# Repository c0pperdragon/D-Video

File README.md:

# D-Video

A system to pump digital video out of vintage home computers.

While there are many mods available to make the video quality of old home computers and consoles
look better on modern displays, most of them are using analog technology (S-Video or RGB or such).
Analog signals are always prone to distortion and some rest of static noise always remains.

To overcome this problem and to get pixel-perfect quality identical to what an emulator could do, 
I have created a system that extracts the video information directly at the pins of the video chip
and transfer this signals to a converter that can generate crisp clear HDMI from it.
Clearly for every computer model there is a different way how to extract video information from the
video chip, and so the converter device must support all different signal types needed. 

That is done by using an FPGA that can be programmed to the meet the specific requirements 
of the system. For this I have designed my on FPGA board which I called the 
D-Video board that is based on a MAX 10 which is a pretty cheap device in comparison
with more powerful chips. With 8K elements and about 380kBit of memory, it just
covers what I need for my projects.

To feed the data into this FPGA, an additional modification board for each computer is needed
that converts the voltages from the pins to 3.3V levels. 

Currently supported devices:
	Atari 800 XL PAL   (probably every 8-bit Atari PAL)

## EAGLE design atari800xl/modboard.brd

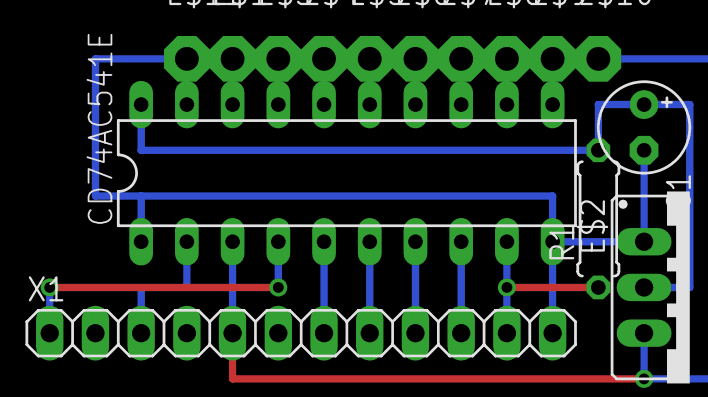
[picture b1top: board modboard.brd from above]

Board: 2 copper layers, 15 parts (0 on the bottom side), 11 nets.

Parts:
C1: 100n; E2,5-5
CD74AC541E: DIL20
E$1, E$3, E$4, E$5, E$6, E$7, E$8, E$9, E$10, E$11: PAD-01
E$2: 78XXS
R1: 1000; 0207/7
X1: 1X12

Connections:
S$1: CD74AC541E.3, E$2.OUT, X1.5
S$2: C1.-, CD74AC541E.1, CD74AC541E.10, CD74AC541E.19
S$3: CD74AC541E.9, R1.1
S$8: CD74AC541E.17, E$3.1
S$9: C1.+, CD74AC541E.20, E$2.GND, R1.2
S$11: CD74AC541E.16, E$4.1
S$12: CD74AC541E.15, E$5.1
S$13: CD74AC541E.14, E$6.1
S$14: CD74AC541E.13, E$7.1
S$15: CD74AC541E.12, E$8.1
S$16: CD74AC541E.11, E$9.1

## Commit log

2016-08-21 :tada: Added .gitattributes & .gitignore files
2016-08-21 Initial check-in
2016-08-25 Redesigned mod board for the Atari 800 XL
2016-09-04 binary file created by quartus (?)
2016-09-11 Teak color detection.
2016-11-18 Split hardware
    Hardware is now divided into Cylcone V GX Starter Kit (the upscaler) and
    a MAX V CPLD (on a DeltaBoard) as the D-Video signal generator.
2016-12-28 Continue implementing GTIA emulation
2016-12-29 Now using the HALT signal to trigger DMA
2017-02-05 Work in progress
2017-02-10 Designed PCB for the C64 mod board
2017-02-19 Last attempt to decode analog signals
    After trying pretty everything, the video signal can not be decoded
    reliably. On color changes the col signal is so distorted that it is not
    possible to find out what the new color of this pixel should be.
2017-02-25 custom fpga board
2017-02-28 Ongoing development fpga board
2017-03-02 finished pcb design
2017-03-21 first working program on the dvideo-board (lead blinker)
2017-03-25 Sucessful run of a test pattern generator
2017-03-29 Integrate GTIA emulation into D-Video board.
2017-03-31 Implemented VDELAY handling
    This was the last of the documented featues of the GTIA. I finally
    included it, even if nobody ever seemed to use it anyway...
2017-04-08 Revision 2 of the D-Video board
    Smaller overall size, GPIO on opposite edge of HDMI plug, mounting
    holes, no input voltage translators
2017-04-09 Restructured code - seperate projects for applications
2017-04-10 Rev. 2 Gerber files
2017-04-29 bill of materials
2017-05-05 Restructured sources
    Make extra folder for shared VHDL code and seperate folder for each
    target computer (atari,c64,spectrum,etc.).
2017-05-25 Ongoing development
    Try to read monitor info.
    Want to bring board Rev.2 to work (no luck yet)
2017-05-27 Made Atari 800 mod run on the Rev.2 board
2017-06-18 Improving signal compatibility
    It seems that many monitors refuse to work with my trick to add/remove a
    few clocks in each frame to synchronize the output to the input.
    Therefore I try to tightly couple the output frequency to the input
    frequency via a PLL. To make this again work, it is necessary to adjust
    the output video timings a bit. I hope this is will be more compliant
    then...
2017-06-23 Tinkering with the Timings for PAL and NTSC
2017-06-25 Use Atari clock to drive the HDMI
    Because the PLL on the D-Video board can not properly lock to the 3.5Mhz
    from the atari pixel clock, I am now using the PAL carrier frequency
    clock (about 4.4Mhz) instead. While this is still a bit out of spec for
    the PLL (5Mhz minimum) this seems to work now.
2017-06-29 Functional version for 3 different screen sizes
    After much fiddling around, I got the mod working for all my displays:
    1280x1024, 1640x1080, 1920x1080, all 50Hz.
    This stretches the standard quite a bit and uses the PLL out of spec,
    but thats the best I can do...
2017-06-30 Clean up and move changes to atarimod rev.2
2017-07-07 General cleanup, Schematics for the Atari modification
2017-07-15 Tweak frame start detection
2018-08-10 more tests...
2018-11-04 Remove trash, resolution tests
2019-05-04 Upscaler from YPbPr to HDML
    Just to have a working test environment to check the output of the YPbPr mod board agains the composite video of the C64.
2019-05-04 Tweak color transformation
2019-06-15 Calibrate for PAL upscaling
    To test the C64 enhancement board, this upscaler takes the PAL YPbPr output from there to scale it to my lcd monitor.
2020-09-10 Reactivate project. 288p mode working nicely.
2020-09-10 Improve sampling timing to about 2ns precision
2020-09-10 Interlace mode
2020-09-13 More fine-tuning to reduce the jitter of the ADC sampling
2021-03-07 Add support for optional YPbPr mode
2021-03-21 Fine-tune YPbPr mode
2022-08-09 Resume work on upscaler
2022-08-10 Get YPbPr conversion working
2022-08-18 Get synchroniation to jittery input signal working.
2023-06-10 Use RGBS for input
